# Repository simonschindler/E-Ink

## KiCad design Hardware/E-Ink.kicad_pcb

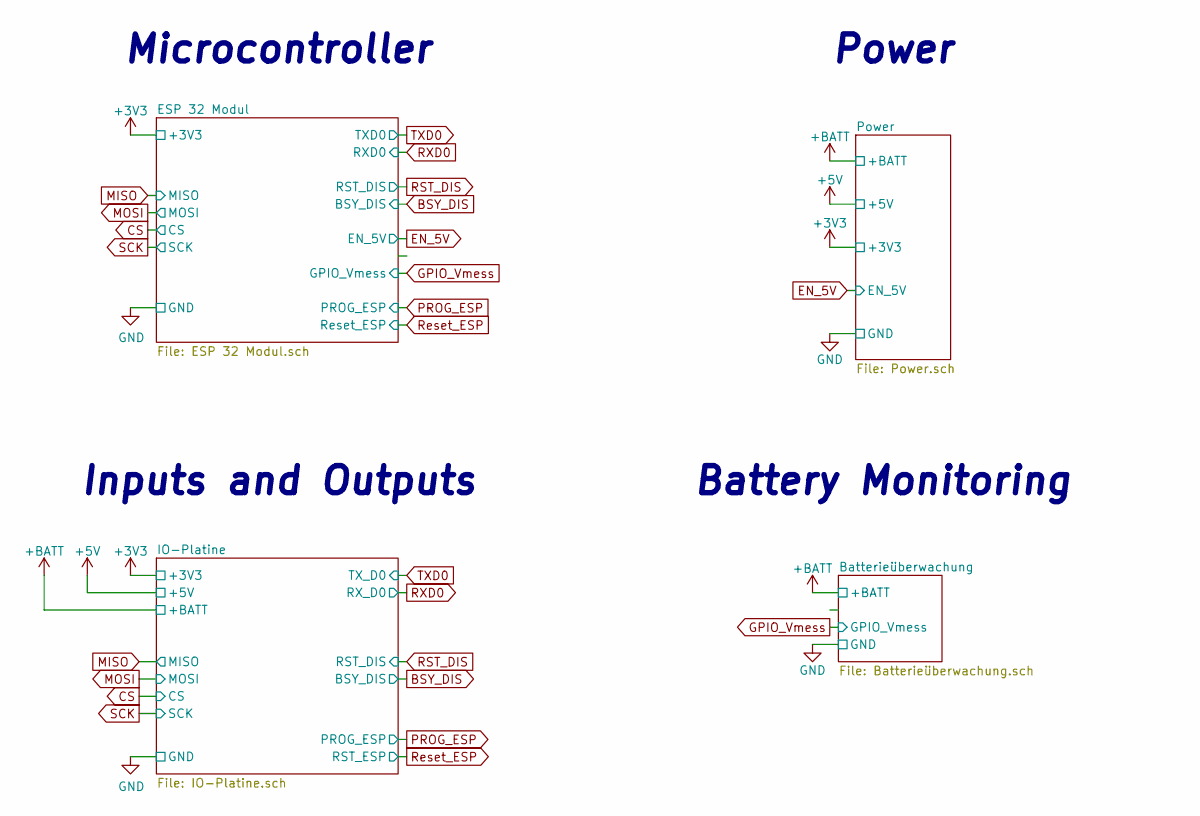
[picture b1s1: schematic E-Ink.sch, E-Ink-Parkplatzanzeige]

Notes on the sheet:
Microcontroller
Power
Inputs and Outputs
Battery Monitoring

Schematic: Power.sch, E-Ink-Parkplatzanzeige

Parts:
C201, C203, C205, C206, C207, C208: 10µ; C_0805_2012Metric_Pad1.15x1.40mm_HandSolder
C202, C204, C209, C210: 100n; C_0805_2012Metric_Pad1.15x1.40mm_HandSolder
L201, L202: 2.2u; L_Taiyo-Yuden_MD-3030; Digi-Key_PN 490-15950-1-ND
Q201: 2N7000; TO-92-3; MPN 2N7000; Digi-Key_PN 2N7000FS-ND
R201: 4k7; R_0805_2012Metric_Pad1.15x1.40mm_HandSolder
R202: 47k; R_0805_2012Metric_Pad1.15x1.40mm_HandSolder
R203, R205, R206: 10k; R_0805_2012Metric_Pad1.15x1.40mm_HandSolder
R204: 100; R_0805_2012Metric_Pad1.15x1.40mm_HandSolder
TP201, TP202: TestPoint; Test_Point_D1.02mm; Digi-Key_PN 36-5001-ND
U201: TPS63002DRCR; Texas_DRC0010J_ThermalVias; Digi-Key_PN 296-19644-1-ND
U202: TPS63031DSKR; WSON-8-1EP_3x3mm_P0.5mm_EP1.6x2.0mm; Digi-Key_PN 296-39461-1-ND

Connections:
+3V3: C205.1, C207.1, C209.1, U202.1 (VOUT), U202.10 (FB); also elsewhere on the board
+5V: C206.1, C208.1, C210.1, TP201.1, U201.1 (VOUT), U201.10 (FB); also elsewhere on the board
+BATT: C201.1, C202.1, C203.1, R204.1, TP202.1, U201.5 (VIN), U202.5 (VIN); also elsewhere on the board
EN_5V: R203.1, U201.6 (EN); also elsewhere on the board
GND: C201.2, C202.2, C203.2, C204.2, C205.2, C206.2, C207.2, C208.2, C209.2, C210.2, R203.2, R205.2, R206.2, U201.3 (PGND), U201.9 (GND), U201.11 (PGND), U202.3 (PGND), U202.9 (GND), U202.11 (PGND); also elsewhere on the board
unnamed: C204.1, U202.6 (EN), U202.8 (VINA)
unnamed: L201.1, U202.4 (L1)
unnamed: L201.2, U202.2 (L2)
unnamed: L202.1, U201.4 (L1)
unnamed: L202.2, U201.2 (L2)
unnamed: R204.2, U201.8 (VINA)
unnamed: R205.1, U202.7 (PS/SYNC)
unnamed: R206.1, U201.7 (PS/SYNC)

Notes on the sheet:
3V3 Buck Boost
5V Buck Boost - Power Supply for Display
MOSFET statt Bipolar

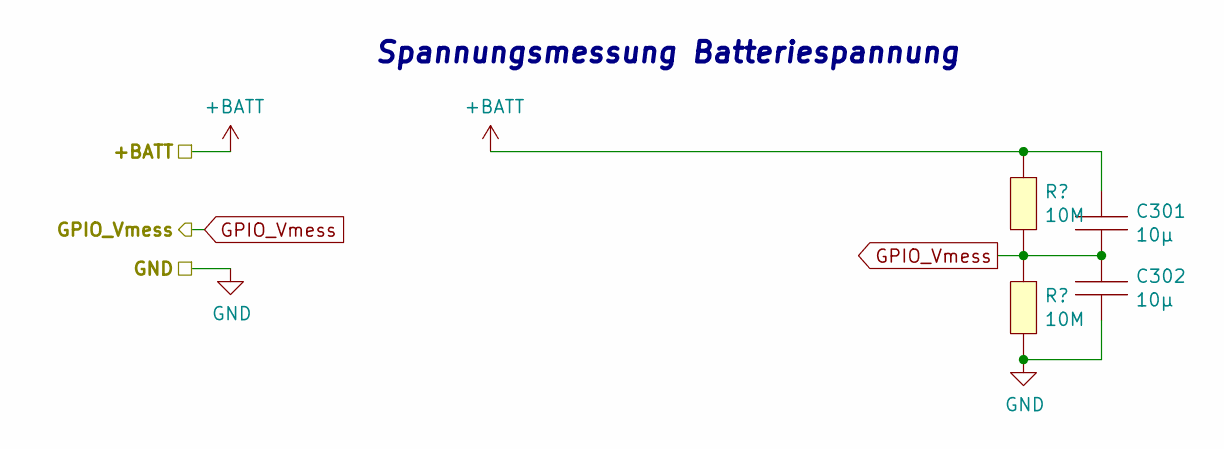
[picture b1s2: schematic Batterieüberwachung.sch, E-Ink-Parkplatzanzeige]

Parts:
C301, C302: 10µ; C_0805_2012Metric_Pad1.15x1.40mm_HandSolder

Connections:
+BATT: C301.1; also elsewhere on the board
GND: C302.2; also elsewhere on the board
GPIO_Vmess: C301.2, C302.1; also elsewhere on the board

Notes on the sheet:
Spannungsmessung Batteriespannung

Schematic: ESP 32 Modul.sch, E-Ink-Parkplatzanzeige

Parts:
C401, C403: 10µ; C_0805_2012Metric_Pad1.15x1.40mm_HandSolder
C402, C404, C405: 100n; C_0805_2012Metric_Pad1.15x1.40mm_HandSolder
R401: 4k7; R_0805_2012Metric_Pad1.15x1.40mm_HandSolder
R402, R403: 0; R_0805_2012Metric_Pad1.15x1.40mm_HandSolder
TP401, TP402, TP403, TP404, TP405, TP406, TP407, TP408, TP409, TP410, TP411, TP412, TP413, TP414: TestPoint; Test_Point_D1.02mm; Digi-Key_PN 36-5001-ND

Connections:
+3V3: C403.1, C404.1, C405.1, R401.1, TP401.1; also elsewhere on the board
CS: TP411.1; also elsewhere on the board
GND: C401.2, C402.2, C403.2, C404.2, C405.2, TP402.1; also elsewhere on the board
GPIO_Vmess: C402.1; also elsewhere on the board
MISO: TP408.1; also elsewhere on the board
MOSI: TP409.1; also elsewhere on the board
unnamed 22: TP403.1; also elsewhere on the board
unnamed 23: TP404.1; also elsewhere on the board
unnamed 24: TP405.1; also elsewhere on the board
unnamed 25: TP406.1; also elsewhere on the board
unnamed 26: TP407.1; also elsewhere on the board
PROG_ESP: TP414.1; also elsewhere on the board
RST_ESP: C401.1, R401.2; also elsewhere on the board
RXD0: TP413.1; also elsewhere on the board
SCK: TP410.1; also elsewhere on the board
TXD0: TP412.1; also elsewhere on the board

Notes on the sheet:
ESP 32 Modul
UART-Programming Interface
SPI-Interface for Communication with Display
Enable the 5V Powersupply for the E-Ink Display
PINS zur späteren evtl. Benutzung

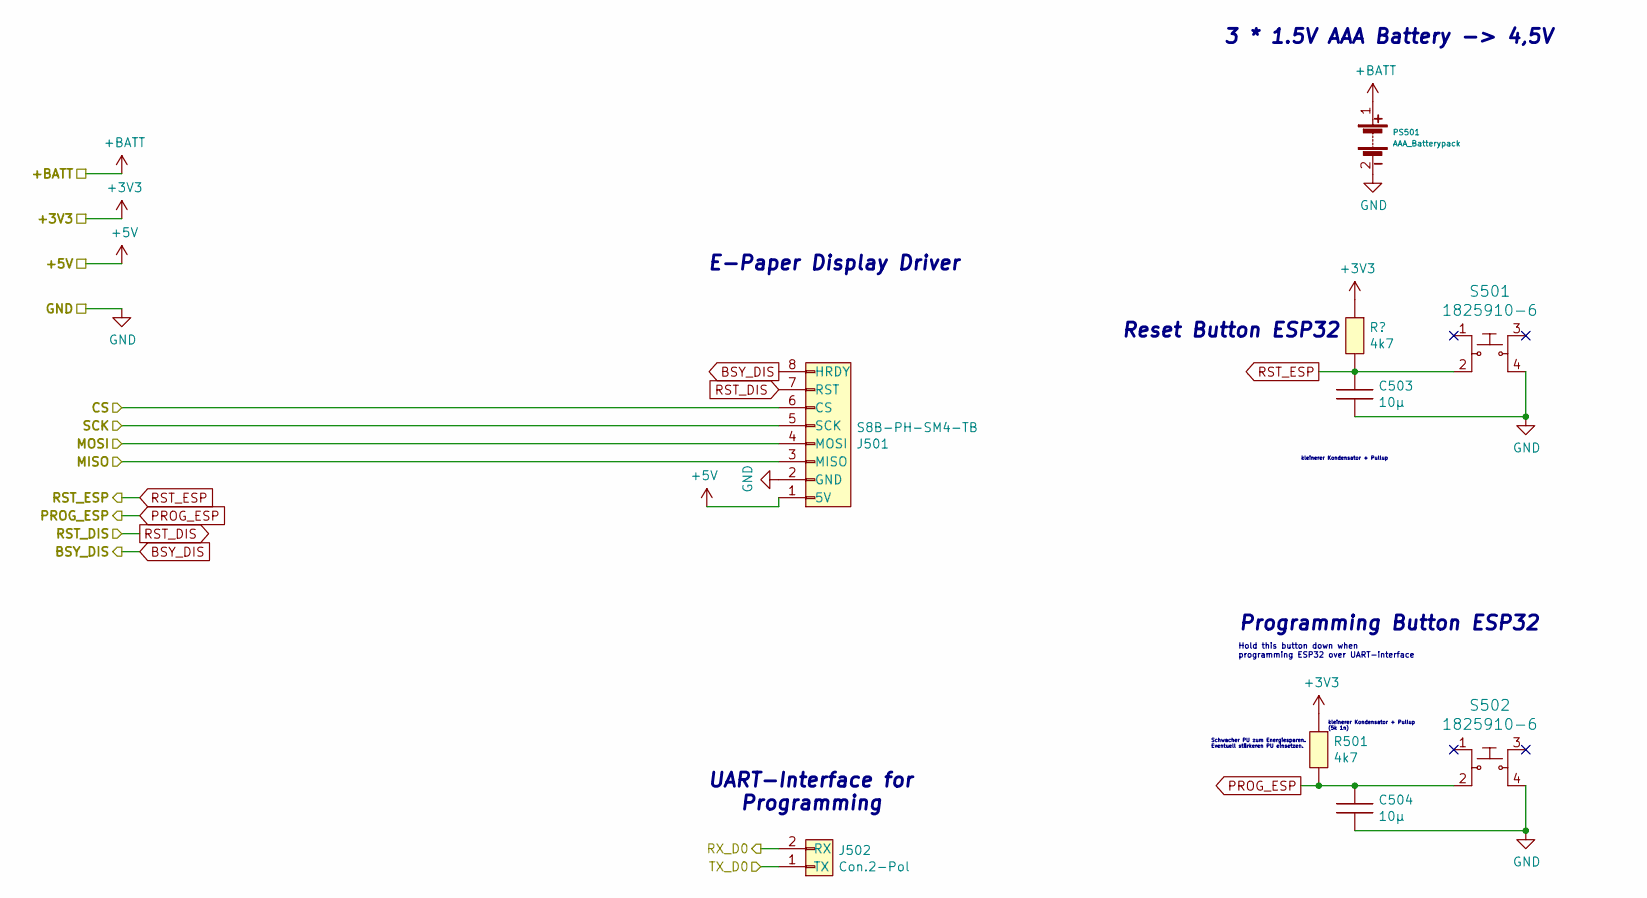
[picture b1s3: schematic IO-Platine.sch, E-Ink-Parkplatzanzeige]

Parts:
C503, C504: 10µ; C_0805_2012Metric_Pad1.15x1.40mm_HandSolder
J501: S8B-PH-SM4-TB; Digi-Key_PN 455-1755-1-ND
J502: Con.2-Pol; Pin-Header_1x2_2.54mm; Digi-Key_PN S5438-ND
PS501: AAA_Batterypack; Pin-Header_1x2_2.54mm
R501: 4k7; R_0805_2012Metric_Pad1.15x1.40mm_HandSolder
S501, S502: 1825910-6; Switch_Tactile_SMD_6x6mm; MPN 1825910-6; Digi-Key_PN 450-1650-ND

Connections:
+3V3: R501.1; also elsewhere on the board
+5V: J501.1 (5V); also elsewhere on the board
+BATT: PS501.1; also elsewhere on the board
BSY_DIS: J501.8 (HRDY); also elsewhere on the board
CS: J501.6 (CS); also elsewhere on the board
GND: C503.2, C504.2, J501.2 (GND), PS501.2, S501.4, S502.4; also elsewhere on the board
MISO: J501.3 (MISO); also elsewhere on the board
MOSI: J501.4 (MOSI); also elsewhere on the board
PROG_ESP: C504.1, R501.2, S502.2; also elsewhere on the board
RST_DIS: J501.7 (RST); also elsewhere on the board
RST_ESP: C503.1, S501.2; also elsewhere on the board
RXD0: J502.2 (RX); also elsewhere on the board
SCK: J501.5 (SCK); also elsewhere on the board
TXD0: J502.1 (TX); also elsewhere on the board

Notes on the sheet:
Reset Button ESP32
Programming Button ESP32
Schwacher PU zum Energiesparen. Eventuell stärkeren PU einsetzen.
Hold this button down when programming ESP32 over UART-interface
E-Paper Display Driver
3 * 1.5V AAA Battery -> 4,5V
UART-Interface for Programming
kleinerer Kondensator + Pullup
kleinerer Kondensator + Pullup (5k 1n)

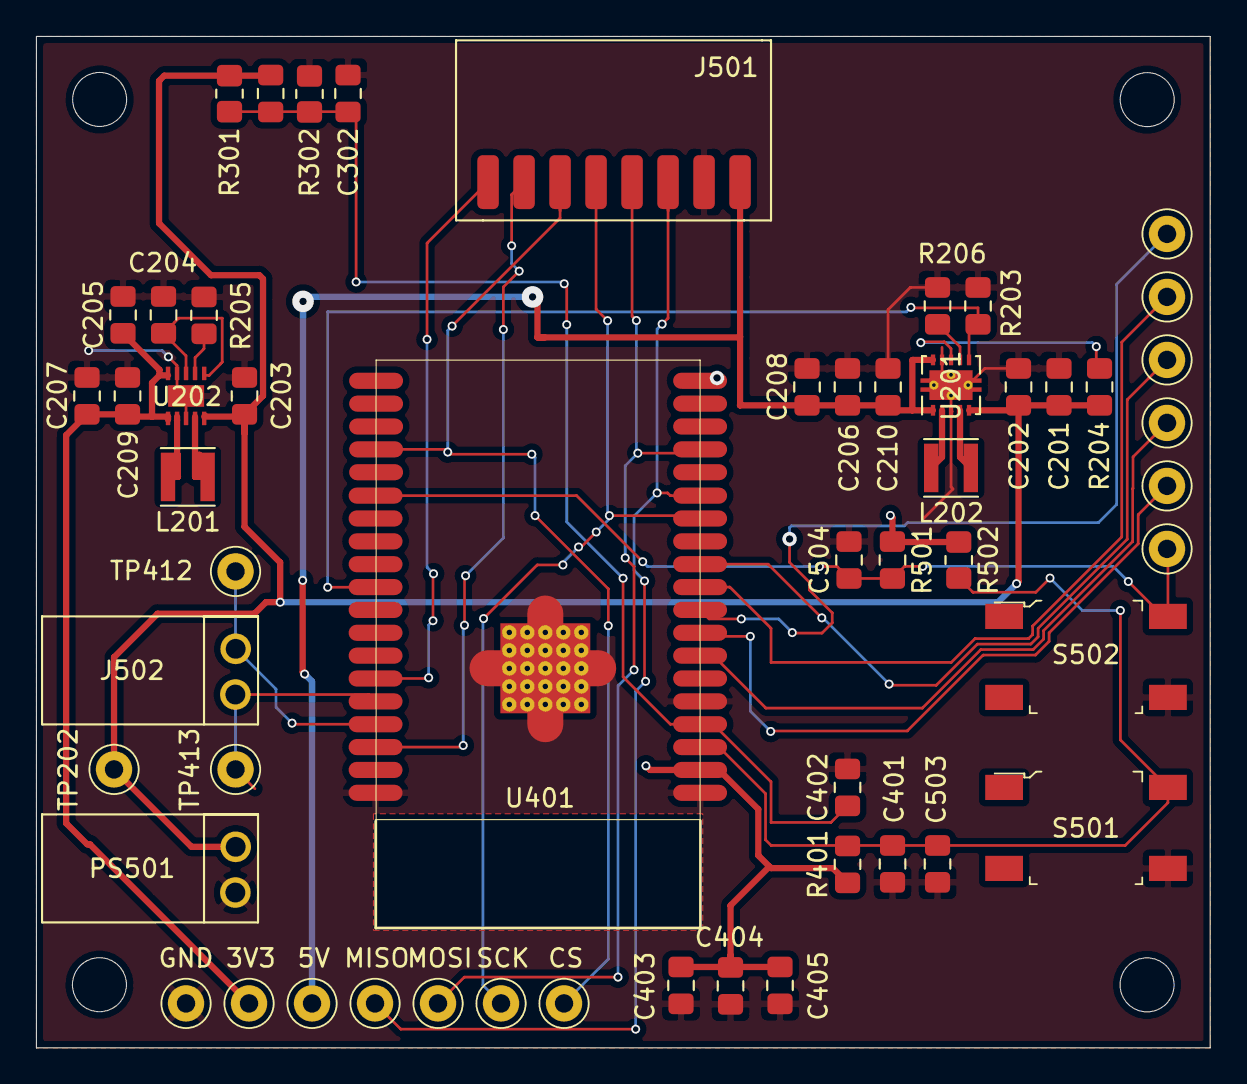
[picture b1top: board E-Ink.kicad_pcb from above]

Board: 2 copper layers, 65.2 x 56.2 mm, 54 parts (0 on the bottom side), 29 nets.

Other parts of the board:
R301, R302: 10M; R_0805_2012Metric_Pad1.20x1.40mm_HandSolder
R502: 4k7; R_0805_2012Metric_Pad1.20x1.40mm_HandSolder
U401: ESP-32-WROOVER-IE; ESP32-WROVER

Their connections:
+3V3: R502.1, U401.2; also elsewhere on the board
+BATT: R301.2; also elsewhere on the board
BSY_DIS: U401.33; also elsewhere on the board
CS: U401.23; also elsewhere on the board
EN_5V: U401.29; also elsewhere on the board
GND: R302.2, U401.1, U401.5, U401.38, U401.39; also elsewhere on the board
GPIO_Vmess: R301.1, R302.1, U401.4; also elsewhere on the board
MISO: U401.14; also elsewhere on the board
MOSI: U401.16; also elsewhere on the board
unnamed 22: U401.11; also elsewhere on the board
unnamed 23: U401.10; also elsewhere on the board
unnamed 24: U401.9; also elsewhere on the board
unnamed 25: U401.8; also elsewhere on the board
unnamed 26: U401.7; also elsewhere on the board
PROG_ESP: U401.25; also elsewhere on the board
RST_DIS: U401.36; also elsewhere on the board
RST_ESP: R502.2, U401.3; also elsewhere on the board
RXD0: U401.34; also elsewhere on the board
SCK: U401.13; also elsewhere on the board
TXD0: U401.35; also elsewhere on the board

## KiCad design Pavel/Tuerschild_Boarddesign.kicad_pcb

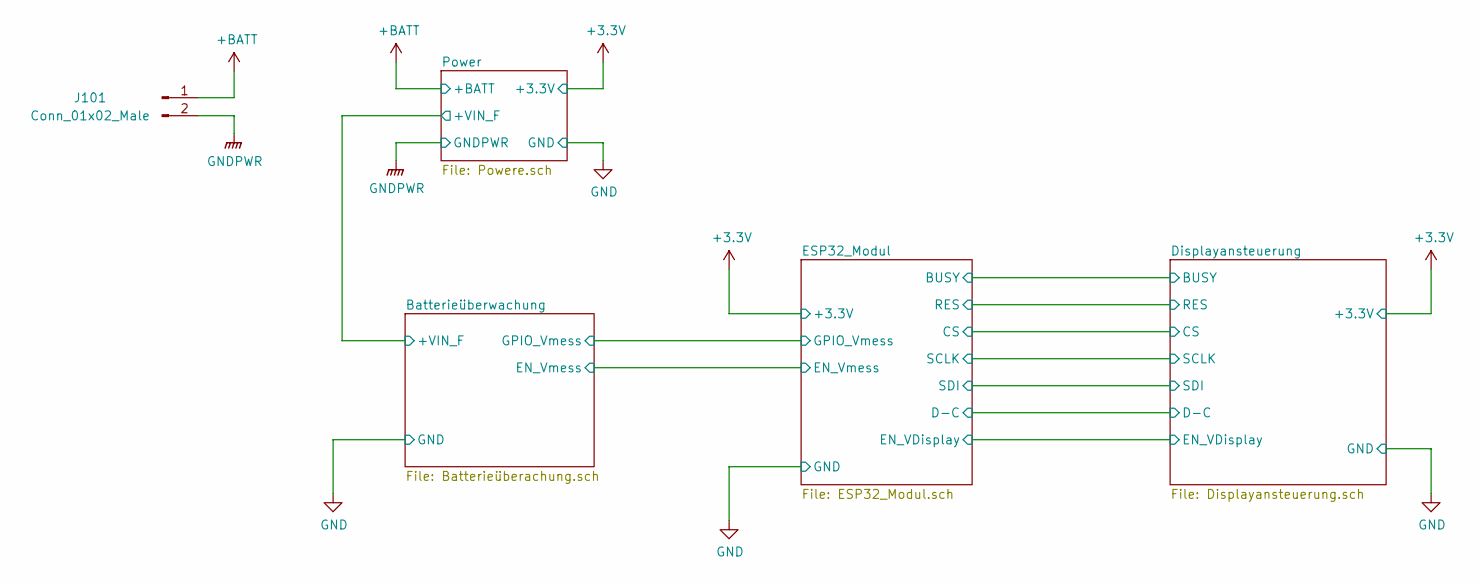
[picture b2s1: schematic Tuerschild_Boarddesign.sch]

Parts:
J101: Conn_01x02_Male; Batterieeinspeisungspads

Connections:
+BATT: J101.1; also elsewhere on the board
GNDPWR: J101.2; also elsewhere on the board

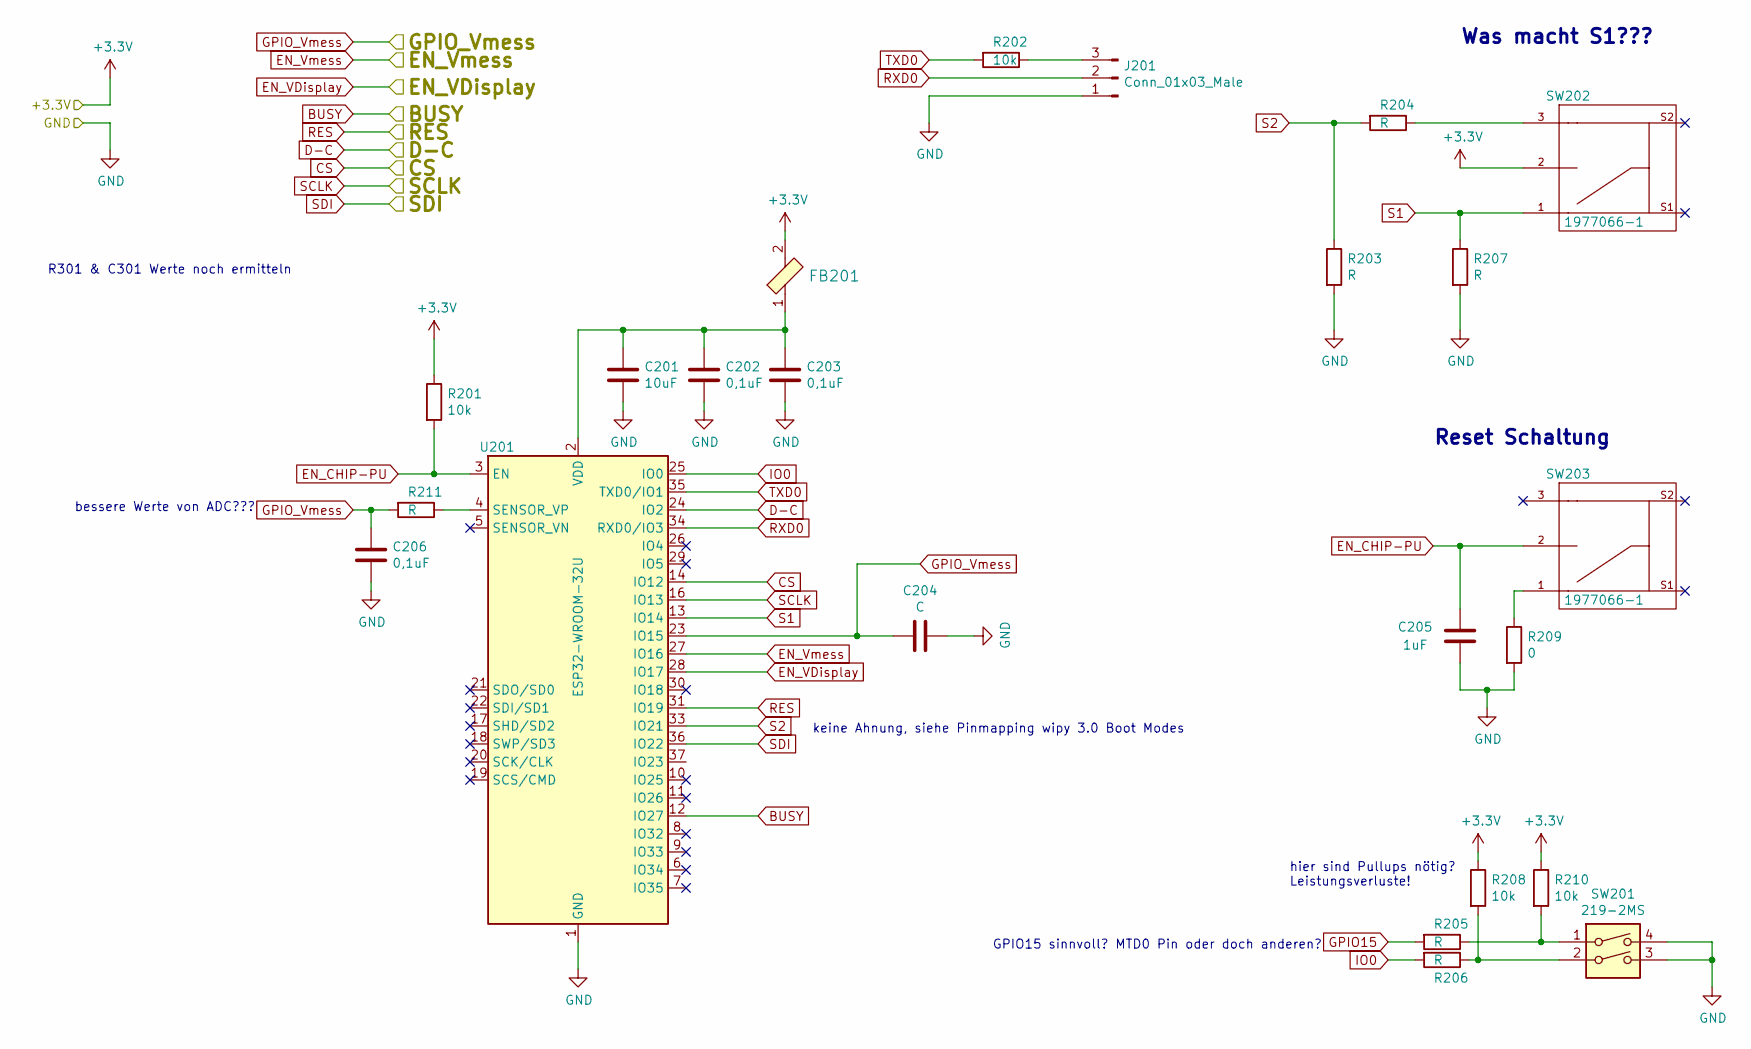
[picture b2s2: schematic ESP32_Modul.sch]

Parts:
C201: 10uF; C_0603_1608Metric
C202, C203, C206: 0,1uF; C_0603_1608Metric
C204: C; C_0603_1608Metric
C205: 1uF; C_0603_1608Metric
FB201: 742792641; 0603; MPN 742792641; Digi-Key_PN 732-1592-2-ND
J201: Conn_01x03_Male; FanPinHeader_1x03_P2.54mm_Vertical
R201, R202, R208, R210: 10k; R_0603_1608Metric_Pad1.05x0.95mm_HandSolder
R203, R204, R205, R206, R207, R211: R; R_0603_1608Metric_Pad1.05x0.95mm_HandSolder
R209: 0; R_0603_1608Metric_Pad1.05x0.95mm_HandSolder
SW201: 219-2MS; SW_DIP_SPSTx02_Slide_6.7x6.64mm_W8.61mm_P2.54mm_LowProfile
SW202, SW203: 1977066-1; TE_1977066-1
U201: ESP32-WROOM-32U

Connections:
+3V3: FB201.2, R201.1, R208.1, R210.1, SW202.2; also elsewhere on the board
BUSY: U201.12 (IO27); also elsewhere on the board
CS: U201.14 (IO12); also elsewhere on the board
D-C: U201.24 (IO2); also elsewhere on the board
EN_CHIP-PU: C205.2, R201.2, SW203.2, U201.3 (EN)
EN_VDisplay: U201.28 (IO17); also elsewhere on the board
EN_Vmess: U201.27 (IO16); also elsewhere on the board
GND: C201.2, C202.2, C203.2, C204.1, C205.1, C206.2, J201.1, R203.2, R207.2, R209.2, SW201.3, SW201.4, U201.1 (GND), U201.15 (GND), U201.38 (GND); also elsewhere on the board
GPIO15: R205.2
GPIO_Vmess: C204.2, C206.1, R211.2, U201.23 (IO15); also elsewhere on the board
IO0: R206.2, U201.25 (IO0)
unnamed: C201.1, C202.1, C203.1, FB201.1, U201.2 (VDD)
unnamed: J201.3, R202.1
unnamed: R204.1, SW202.3 (1)
unnamed: R205.1, R210.2, SW201.1
unnamed: R206.1, R208.2, SW201.2
unnamed: R209.1, SW203.1
unnamed: R211.1, U201.4 (SENSOR_VP)
RES: U201.31 (IO19); also elsewhere on the board
RXD0: J201.2, U201.34 (RXD0/IO3)
S1: R207.1, SW202.1, U201.13 (IO14)
S2: R203.1, R204.2, U201.33 (IO21)
SCLK: U201.16 (IO13); also elsewhere on the board
SDI: U201.36 (IO22); also elsewhere on the board
TXD0: R202.2, U201.35 (TXD0/IO1)

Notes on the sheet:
R301 & C301 Werte noch ermitteln
Reset Schaltung
Was macht S1???
hier sind Pullups nötig? Leistungsverluste!
keine Ahnung, siehe Pinmapping wipy 3.0 Boot Modes
bessere Werte von ADC???
GPIO15 sinnvoll? MTD0 Pin oder doch anderen?

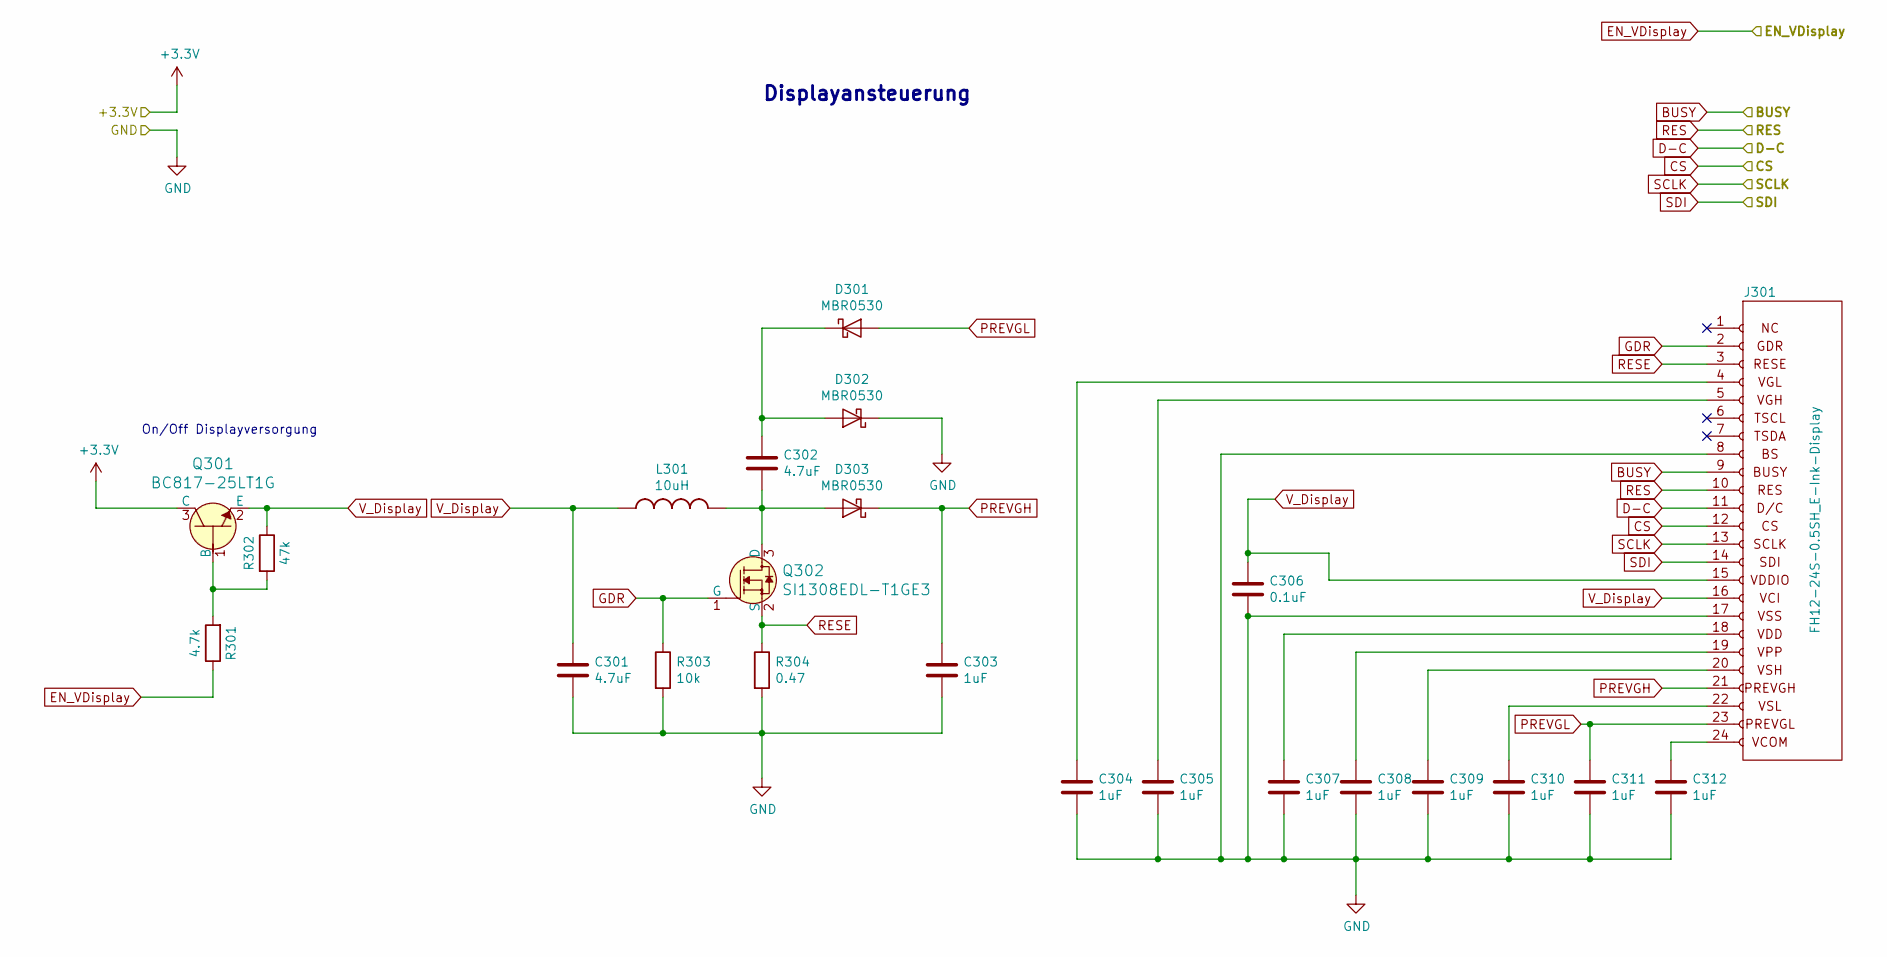
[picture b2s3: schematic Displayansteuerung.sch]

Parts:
C301, C302: 4.7uF; C_0603_1608Metric
C303, C304, C305, C307, C308, C309, C310, C311, C312: 1uF; C_0603_1608Metric
C306: 0.1uF; C_0603_1608Metric
D301, D302, D303: MBR0530; D_SOD-123
J301: FH12-24S-0.5SH_E-Ink-Display; Hirose_FH12-24S-0.5SH_1x24-1MP_P0.50mm_Horizontal
L301: 10uH; NLCV32-EF
Q301: BC817-25LT1G; SOT-23; MPN BC817-25LT1G; Digi-Key_PN BC817-25LT1GOSCT-ND
Q302: SI1308EDL-T1GE3; SOT-323_SC-70; MPN SI1308EDL-T1-GE3; Digi-Key_PN SI1308EDL-T1-GE3CT-ND
R301: 4.7k; R_0603_1608Metric_Pad1.05x0.95mm_HandSolder
R302: 47k; R_0603_1608Metric_Pad1.05x0.95mm_HandSolder
R303: 10k; R_0603_1608Metric_Pad1.05x0.95mm_HandSolder
R304: 0.47; R_0603_1608Metric_Pad1.05x0.95mm_HandSolder

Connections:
+3V3: Q301.3 (C); also elsewhere on the board
BUSY: J301.9; also elsewhere on the board
CS: J301.12; also elsewhere on the board
D-C: J301.11; also elsewhere on the board
EN_VDisplay: R301.1; also elsewhere on the board
GDR: J301.2, Q302.1 (G), R303.1
GND: C301.2, C303.2, C304.2, C305.2, C306.2, C307.2, C308.2, C309.2, C310.2, C311.2, C312.2, D302.1 (K), J301.8, J301.17, R303.2, R304.2; also elsewhere on the board
unnamed: C302.1, D301.1 (K), D302.2 (A)
unnamed: C302.2, D303.2 (A), L301.2, Q302.3 (D)
unnamed: C304.1, J301.4
unnamed: C305.1, J301.5
unnamed: C307.1, J301.18
unnamed: C308.1, J301.19
unnamed: C309.1, J301.20
unnamed: C310.1, J301.22
unnamed: C312.1, J301.24
unnamed: Q301.1 (B), R301.2, R302.2
PREVGH: C303.1, D303.1 (K), J301.21
PREVGL: C311.1, D301.2 (A), J301.23
RES: J301.10; also elsewhere on the board
RESE: J301.3, Q302.2 (S), R304.1
SCLK: J301.13; also elsewhere on the board
SDI: J301.14; also elsewhere on the board
V_Display: C301.1, C306.1, J301.15, J301.16, L301.1, Q301.2 (E), R302.1

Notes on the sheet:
On/Off Displayversorgung
Displayansteuerung

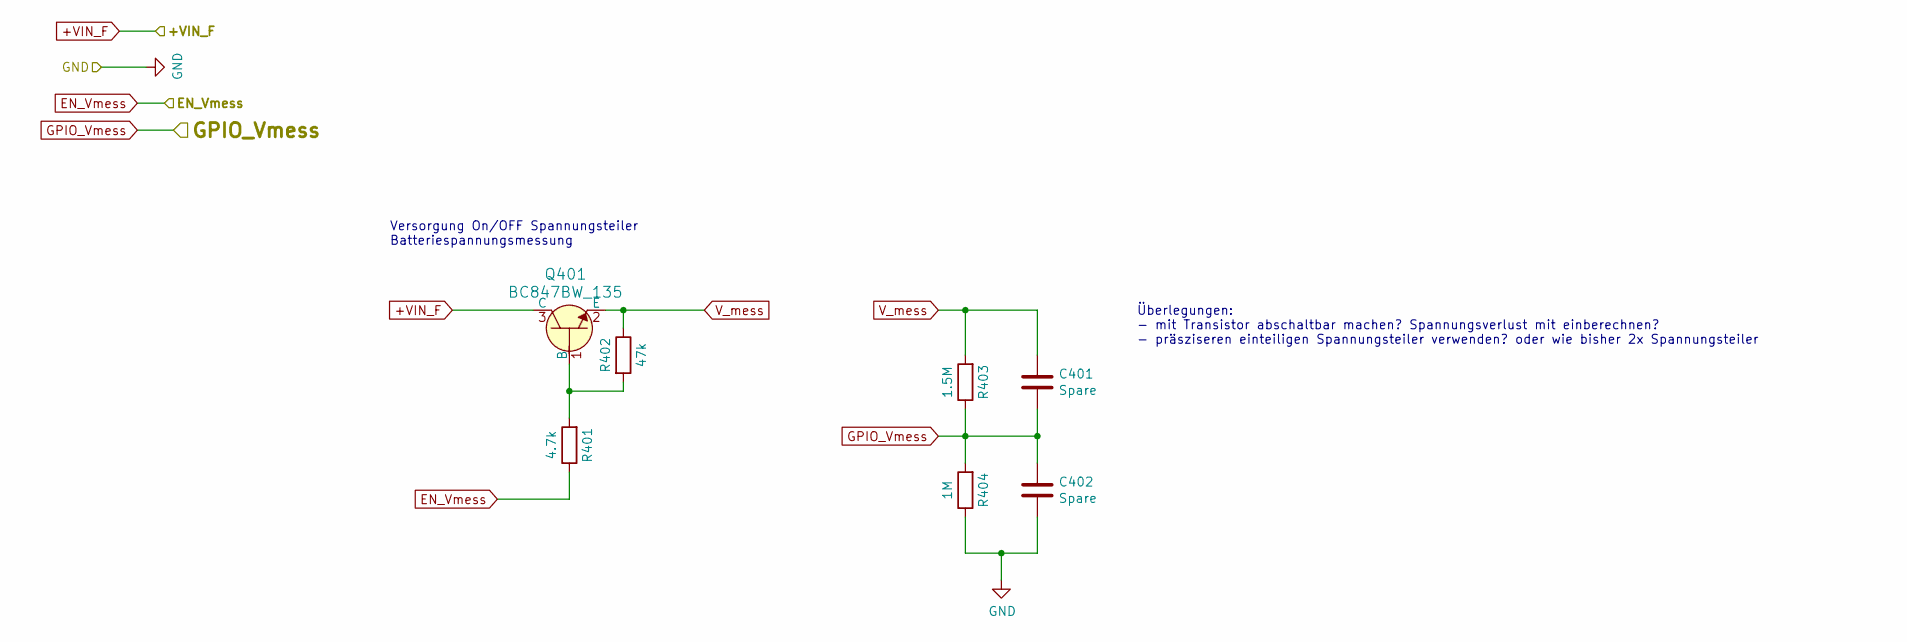
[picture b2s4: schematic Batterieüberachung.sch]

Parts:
C401, C402: Spare; C_0603_1608Metric
Q401: BC847BW_135; SOT-323_SC-70_Handsoldering; MPN BC847BW,135; Digi-Key_PN 1727-6192-6-ND
R401: 4.7k; R_0603_1608Metric_Pad1.05x0.95mm_HandSolder
R402: 47k; R_0603_1608Metric_Pad1.05x0.95mm_HandSolder
R403: 1.5M; R_0603_1608Metric_Pad1.05x0.95mm_HandSolder
R404: 1M; R_0603_1608Metric_Pad1.05x0.95mm_HandSolder

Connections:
+VIN_F: Q401.3 (C); also elsewhere on the board
EN_Vmess: R401.1; also elsewhere on the board
GND: C402.2, R404.1; also elsewhere on the board
GPIO_Vmess: C401.2, C402.1, R403.1, R404.2; also elsewhere on the board
unnamed: Q401.1 (B), R401.2, R402.2
V_mess: C401.1, Q401.2 (E), R402.1, R403.2

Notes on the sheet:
Versorgung On/OFF Spannungsteiler Batteriespannungsmessung
Überlegungen: - mit Transistor abschaltbar machen? Spannungsverlust mit einberechnen? - präsziseren einteiligen Spannungsteiler verwenden? oder wie bisher 2x Spannungsteiler

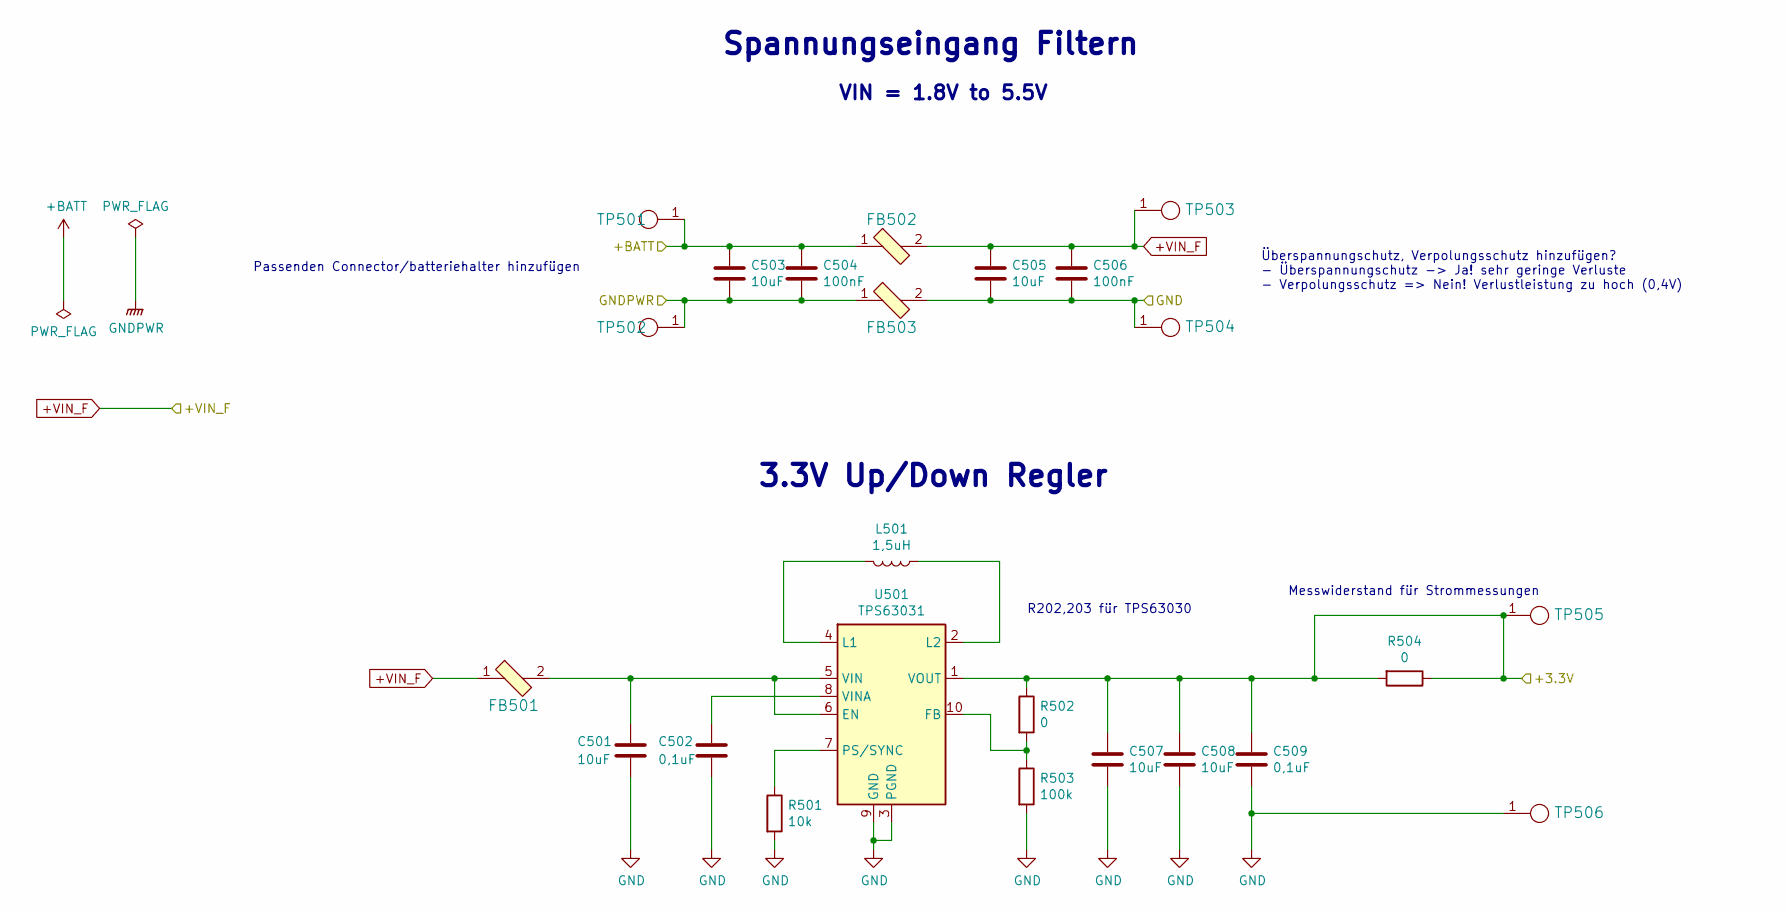
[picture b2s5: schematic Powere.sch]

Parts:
C501, C507, C508: 10uF; C_0603_1608Metric
C502, C509: 0,1uF; C_0603_1608Metric
C503, C505: 10uF; C_0805_2012Metric_Pad1.15x1.40mm_HandSolder
C504, C506: 100nF; C_0603_1608Metric
FB501, FB502, FB503: 742792641; 0603; MPN 742792641; Digi-Key_PN 732-1592-2-ND
L501: 1,5uH; LPS3015_Coilcraft
R501: 10k; R_0603_1608Metric_Pad1.05x0.95mm_HandSolder
R502, R504: 0; R_0603_1608Metric_Pad1.05x0.95mm_HandSolder
R503: 100k; R_0603_1608Metric_Pad1.05x0.95mm_HandSolder
TP501, TP502, TP503, TP504, TP505, TP506: Testpunkt_small; TestPoint_Pad_D1.5mm
U501: TPS63031; Texas_TPS6303x_ThermalVias

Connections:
+3V3: C507.1, C508.1, C509.1, R502.1, R504.1, R504.2, TP505.1, U501.1 (VOUT); also elsewhere on the board
+BATT: C503.1, C504.1, FB502.1, TP501.1; also elsewhere on the board
+VIN_F: C505.1, C506.1, FB501.1, FB502.2, TP503.1; also elsewhere on the board
GND: C501.2, C502.2, C505.2, C506.2, C507.2, C508.2, C509.2, FB503.2, R501.2, R503.2, TP504.1, TP506.1, U501.3 (PGND), U501.9 (GND), U501.11 (PGND); also elsewhere on the board
GNDPWR: C503.2, C504.2, FB503.1, TP502.1; also elsewhere on the board
unnamed: C501.1, FB501.2, U501.5 (VIN), U501.6 (EN)
unnamed: C502.1, U501.8 (VINA)
unnamed: L501.1, U501.2 (L2)
unnamed: L501.2, U501.4 (L1)
unnamed: R501.1, U501.7 (PS/SYNC)
unnamed: R502.2, R503.1, U501.10 (FB)

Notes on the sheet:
Passenden Connector/batteriehalter hinzufügen
Spannungseingang Filtern
VIN = 1.8V to 5.5V
3.3V Up/Down Regler
Überspannungschutz, Verpolungsschutz hinzufügen? - Überspannungschutz -> Ja! sehr geringe Verluste - Verpolungsschutz => Nein! Verlustleistung zu hoch (0,4V)
R202,203 für TPS63030
Messwiderstand für Strommessungen

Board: 2 copper layers, 78 parts (0 on the bottom side), 50 nets, no tracks yet.

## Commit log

2019-11-11 Added Hardware
2019-11-11 Added ESP32-WROOM-32U to sch-lib
2019-11-11 Added stuff
2019-11-11 Added LDOs and RPi Header
2019-11-21 safe commit
2019-11-21 save work @arges
2019-11-22 Save commit after work at OTH
2019-11-25 Zwischenspeichern
2019-11-25 save work at oth
2019-11-27 save commit again
2019-11-27 saving the world
2019-11-29 save commit
2019-12-02 save commit from work at night
2019-12-02 Save work from OTH
2019-12-05 Martin ist unförmig
2019-12-09 Konstruktion Frontpanel begonnen.
2019-12-10 Durchführung Flexkabel und Stege für die Platinenhalterung hinzugefügt.
2019-12-12 Ich hoffe wir koennen jetzt den Master mergen!
2019-12-12 Zwischenspeicher Arbeit OTH
2019-12-13 - Ordner "Links" für Teile DigiKey hinzugefügt - Konstruktion Batteriefach.FCStd begonnen - Konstruktion Rückdeckel.FCStd begonnen
2019-12-13 save work at arges, finished layout and routing
2019-12-15 savecommit
2019-12-17 -Batteriefach: Maße Batteriafach nochmal angepasst + Lage Führung Einschub verändert -Assembly-Datei für groben Zusammenbau eingefügt
2019-12-18 -Batteriefach: Position Bohrung verändert -Rückdeckel: Stege Einschub hinzugefügt -Konstruktion: Verriegelungsstift begonnen
2019-12-20 finished PCB and ordered
2020-02-17 Aenderungen Bestellliste begonnen
2020-02-17 Gehaeusekomponenten hinzugefuegt
2020-03-10 Batteriefach überarbeitet
2020-03-13 groessere Bohrung Entriegelung
2020-03-20 Rückdeckel: Aufnahme für Kontaktpads hinzugefügt und Einschub an aktuelle Groeße des Batteriefachs angepasstTestfrontpanel und Testrückdeckel für Clipverschluss erstellt
2020-04-28 Step-Dateien für Druck exportiert.
2020-05-02 Rückdeckel um Clips erweitert; Frontpanel um Durchführung für Clips erweitert; Stepdateien für Druck und Fräse exportiert
2020-06-19 esp works
2020-07-03 Auflage für das Display nochmals angepasst, da zu klein
2020-07-10 save for Arges Session
2020-07-10 Save work at Arges
2020-07-17 Save work at rgb
2020-10-20 Added new MCU and redesigned schematics
2020-10-20 finished PCB, Thursday Review with Lukas
2020-12-18 restart Hardware
2020-12-18 added glascover and holding system
2020-12-19 added all changes just to make sure
2020-12-21 renaming and small change to glasabdeckung.fcstd
2020-12-25 everything works now as it should. Merry XMAS
